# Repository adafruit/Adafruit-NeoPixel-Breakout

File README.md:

## Adafruit NeoPixel Breakout with JST SH Connectors PCB

<a href="http://www.adafruit.com/products/5975"><br/>
Click here to purchase one from the Adafruit shop</a>

PCB files for the Adafruit NeoPixel Breakout with JST SH Connectors. 

Format is EagleCAD schematic and board layout
* https://www.adafruit.com/product/5975

### Description

This little breakout makes it easy to add a single NeoPixel to a project, with mounting holes and a pluggable connector. The PCB is less than 0.5"x0.5" and comes with two 3-pin JST SH 1mm pitch connectors for input and output. On the opposite side, a 5050 (5mm square) classic RGB NeoPixel that can be powered and controlled with 3.3V or 5V power.

The two mounting holes are M2 size and have clearance for the screw head, or could be used for sewing onto a fabric backing or attaching to a small model. Of course this design will never be as affordable as a pre-made strand with dozens of LEDs, but there's probably some time it would be useful - especially since it can be easily swapped out.

Comes as a single NeoPixel, no cables included so check out our JST SH compatible cables in plug or socket.

### License

Adafruit invests time and resources providing this open source design, please support Adafruit and open-source hardware by purchasing products from [Adafruit](https://www.adafruit.com)!

Designed by Limor Fried/Ladyada for Adafruit Industries.

Creative Commons Attribution/Share-Alike, all text above must be included in any redistribution. 
See license.txt for additional details.

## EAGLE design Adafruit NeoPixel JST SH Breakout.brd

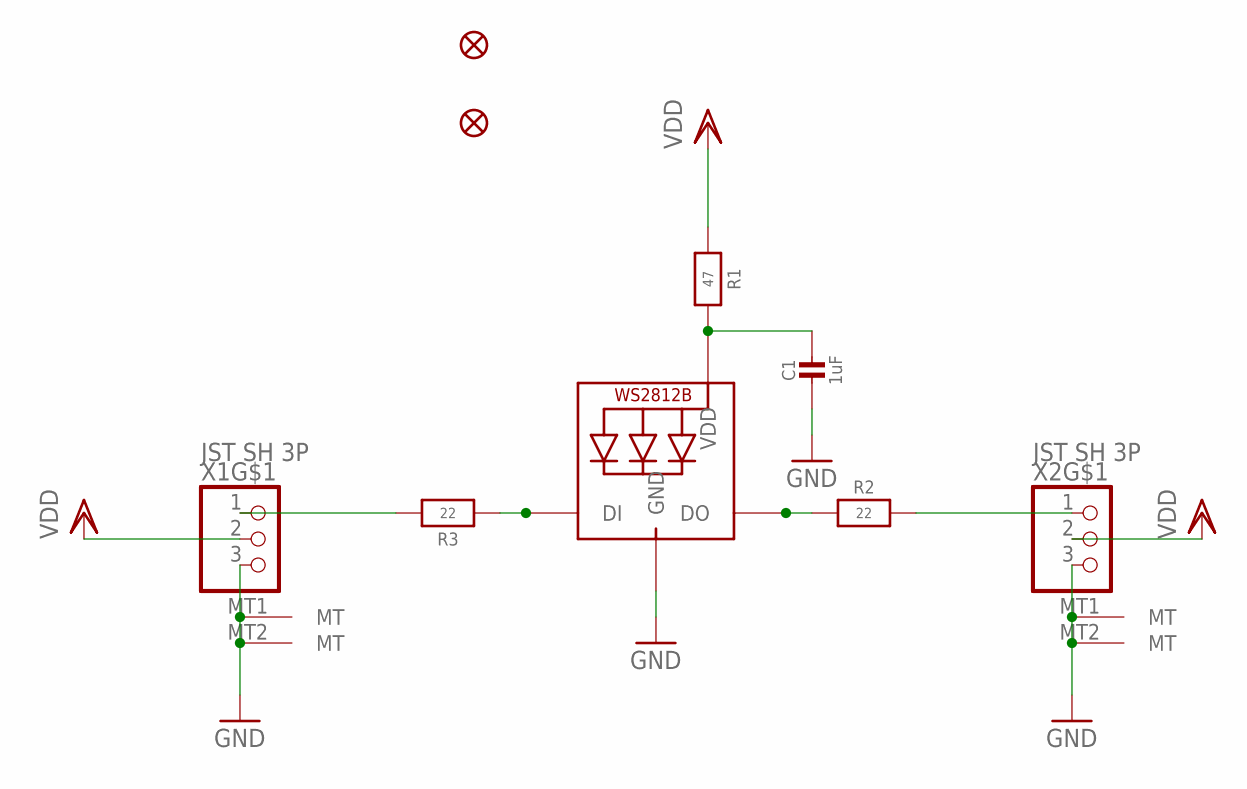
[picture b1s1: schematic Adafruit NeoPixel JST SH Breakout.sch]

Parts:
C1: 1uF; 0603-NO
FID1, FID2: FIDUCIAL_0.5MM
LED2: WS2812B_5050N; WS2812B-NARROW
R1: 47; _0402NO
R2, R3: 22; _0402NO
X1, X2: JST SH 3P; JST_SH3

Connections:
GND: C1.2, LED2.3-GND (GND), X1.3, X1.MT1 (MT), X1.MT2 (MT), X2.3, X2.MT1 (MT), X2.MT2 (MT)
IN: R3.2, X1.1
unnamed: LED2.2-DOUT (DO), R2.1
unnamed: LED2.4-DIN (DI), R3.1
unnamed: C1.1, LED2.1-VDD (VDD), R1.2
OUT: R2.2, X2.1
VDD: R1.1, X1.2, X2.2

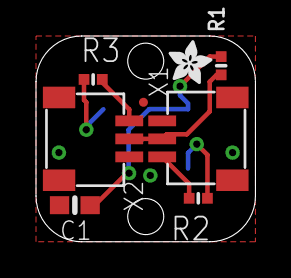
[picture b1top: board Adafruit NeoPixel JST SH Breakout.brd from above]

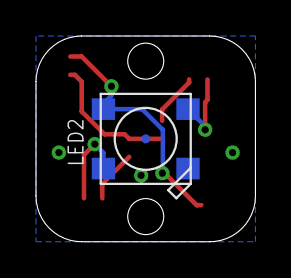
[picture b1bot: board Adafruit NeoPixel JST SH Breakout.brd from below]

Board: 2 copper layers, 12.2 x 11.4 mm, 13 parts (2 on the bottom side), 7 nets.

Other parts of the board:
PLABEL0: PLABEL0
PLABEL1: PLABEL1
PLABEL2: PLABEL2
U$1: ADAFRUIT_2.5MM

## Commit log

2024-06-13 cookiecutter

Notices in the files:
parts and their libraries:
microbuilder: This work is placed in the public domain, and may be freely used for commercial and non-commercial work with the following conditions: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
